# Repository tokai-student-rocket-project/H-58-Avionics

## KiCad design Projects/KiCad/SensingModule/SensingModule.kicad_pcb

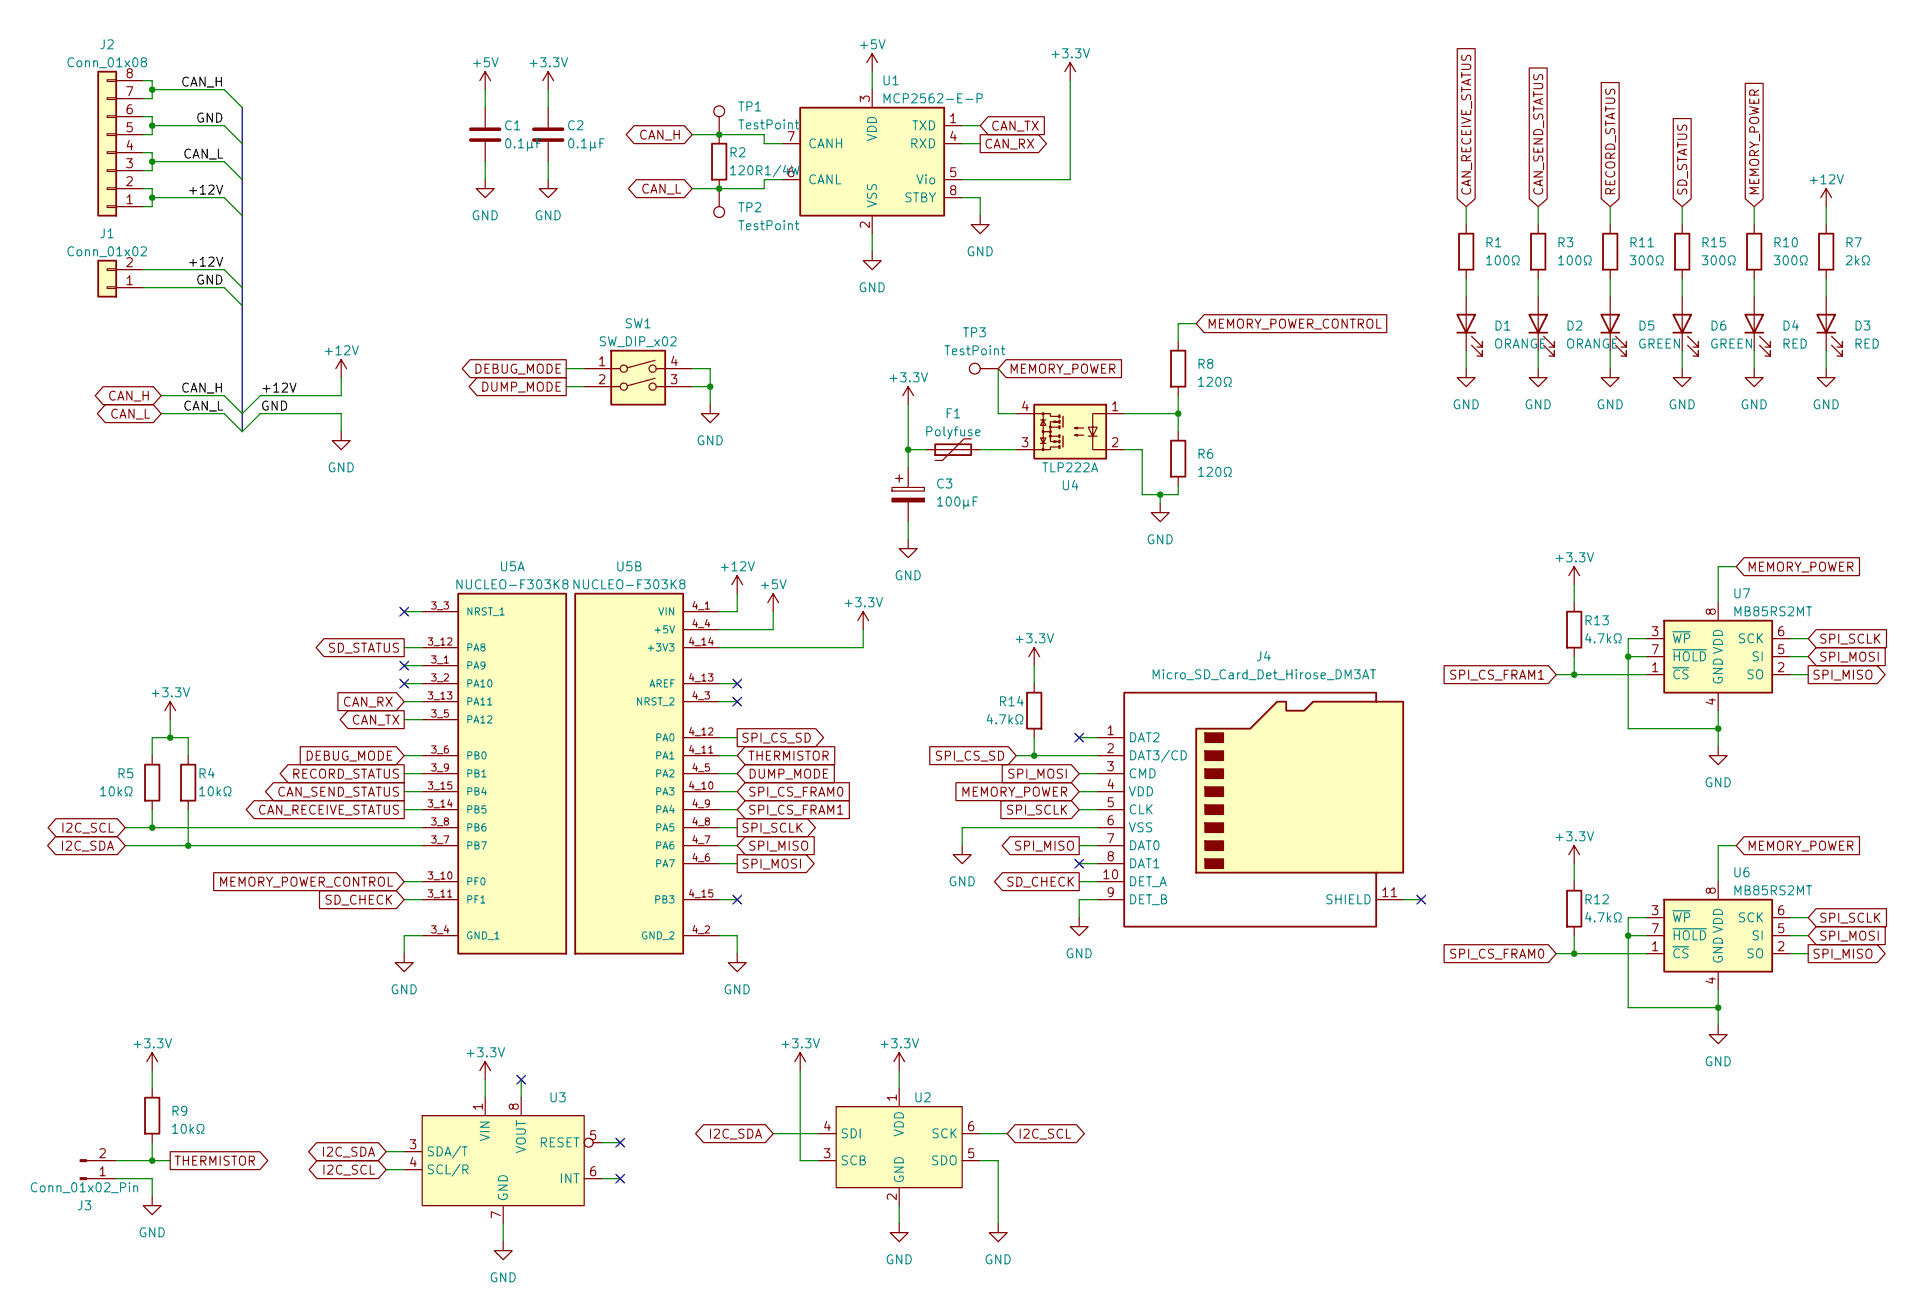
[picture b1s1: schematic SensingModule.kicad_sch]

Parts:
C1, C2: 0.1μF; C_0805_2012Metric_Pad1.18x1.45mm_HandSolder
C3: 100μF; CP_Elec_6.3x7.7
D1, D2: ORANGE; LED_0603_1608Metric_Pad1.05x0.95mm_HandSolder
D3, D4: RED; LED_0603_1608Metric_Pad1.05x0.95mm_HandSolder
D5, D6: GREEN; LED_0603_1608Metric_Pad1.05x0.95mm_HandSolder
F1: Polyfuse; Fuse_1206_3216Metric_Pad1.42x1.75mm_HandSolder
J1: Conn_01x02; Hirose_DF1B
J2: Conn_01x08; Hirose_DF11-8DP-2DSA_2x04_P2.00mm_Vertical
J3: Conn_01x02_Pin; Hirose_DF1B
J4: Micro_SD_Card_Det_Hirose_DM3AT; microSD_HC_Hirose_DM3AT-SF-PEJM5
R1, R3: 100Ω; R_0603_1608Metric_Pad0.98x0.95mm_HandSolder
R2: 120R1/4W; R_0603_1608Metric_Pad0.98x0.95mm_HandSolder
R4, R5, R9: 10kΩ; R_0603_1608Metric_Pad0.98x0.95mm_HandSolder
R6, R8: 120Ω; R_0603_1608Metric_Pad0.98x0.95mm_HandSolder
R7: 2kΩ; R_0603_1608Metric_Pad0.98x0.95mm_HandSolder
R10, R11, R15: 300Ω; R_0603_1608Metric_Pad0.98x0.95mm_HandSolder
R12, R13, R14: 4.7kΩ; R_0603_1608Metric_Pad0.98x0.95mm_HandSolder
SW1: SW_DIP_x02; SW_DIP_SPSTx02_Piano_10.8x6.64mm_W7.62mm_P2.54mm
TP1, TP2, TP3: TestPoint; Pin_D1.0mm_L10.0mm
U1: MCP2562-E-P; DIP-8_W7.62mm
U2: BME280
U3: BNO055
U4: TLP222A; DIP-4_W7.62mm
U5: NUCLEO-F303K8; MODULE_NUCLEO-F303K8; PARTREV 5
U6, U7: MB85RS2MT; DIP-8_W7.62mm

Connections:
+3.3V: C2.1, C3.1, F1.1, R4.1, R5.1, R9.1, R12.1, R13.1, R14.1, U1.5 (Vio), U2.1 (VDD), U2.3 (SCB), U3.1 (VIN), U5.4_14 (+3V3)
+5V: C1.1, U1.3 (VDD), U5.4_4 (+5V)
+12V: J1.2, J2.1, J2.2, R7.1, U5.4_1 (VIN)
CAN_H: J2.7, J2.8, R2.1, TP1.1, U1.7 (CANH)
CAN_L: J2.3, J2.4, R2.2, TP2.1, U1.6 (CANL)
CAN_RECEIVE_STATUS: R1.1, U5.3_14 (PB5)
CAN_RX: U1.4 (RXD), U5.3_13 (PA11)
CAN_SEND_STATUS: R3.1, U5.3_15 (PB4)
CAN_TX: U1.1 (TXD), U5.3_5 (PA12)
DEBUG_MODE: SW1.1, U5.3_6 (PB0)
DUMP_MODE: SW1.2, U5.4_5 (PA2)
GND: C1.2, C2.2, C3.2, D1.1 (K), D2.1 (K), D3.1 (K), D4.1 (K), D5.1 (K), D6.1 (K), J1.1, J2.5, J2.6, J3.1, J4.6 (VSS), J4.9 (DET_B), R6.2, SW1.3, SW1.4, U1.2 (VSS), U1.8 (STBY), U2.2 (GND), U2.5 (SDO), U3.7 (GND), U4.2, U5.3_4 (GND_1), U5.4_2 (GND_2), U6.3 (~WP), U6.4 (GND), U6.7 (~HOLD), U7.3 (~WP), U7.4 (GND), U7.7 (~HOLD)
I2C_SCL: R5.2, U2.6 (SCK), U3.4 (SCL/R), U5.3_8 (PB6)
I2C_SDA: R4.2, U2.4 (SDI), U3.3 (SDA/T), U5.3_7 (PB7)
MEMORY_POWER: J4.4 (VDD), R10.1, TP3.1, U4.4, U6.8 (VDD), U7.8 (VDD)
MEMORY_POWER_CONTROL: R8.1, U5.3_10 (PF0)
unnamed: D1.2 (A), R1.2
unnamed: D2.2 (A), R3.2
unnamed: D3.2 (A), R7.2
unnamed: D4.2 (A), R10.2
unnamed: D5.2 (A), R11.2
unnamed: D6.2 (A), R15.2
unnamed: F1.2, U4.3
unnamed: R6.1, R8.2, U4.1
RECORD_STATUS: R11.1, U5.3_9 (PB1)
SD_CHECK: J4.10 (DET_A), U5.3_11 (PF1)
SD_STATUS: R15.1, U5.3_12 (PA8)
SPI_CS_FRAM0: R12.2, U5.4_10 (PA3), U6.1 (~CS)
SPI_CS_FRAM1: R13.2, U5.4_9 (PA4), U7.1 (~CS)
SPI_CS_SD: J4.2 (DAT3/CD), R14.2, U5.4_12 (PA0)
SPI_MISO: J4.7 (DAT0), U5.4_7 (PA6), U6.2 (SO), U7.2 (SO)
SPI_MOSI: J4.3 (CMD), U5.4_6 (PA7), U6.5 (SI), U7.5 (SI)
SPI_SCLK: J4.5 (CLK), U5.4_8 (PA5), U6.6 (SCK), U7.6 (SCK)
THERMISTOR: J3.2, R9.2, U5.4_11 (PA1)

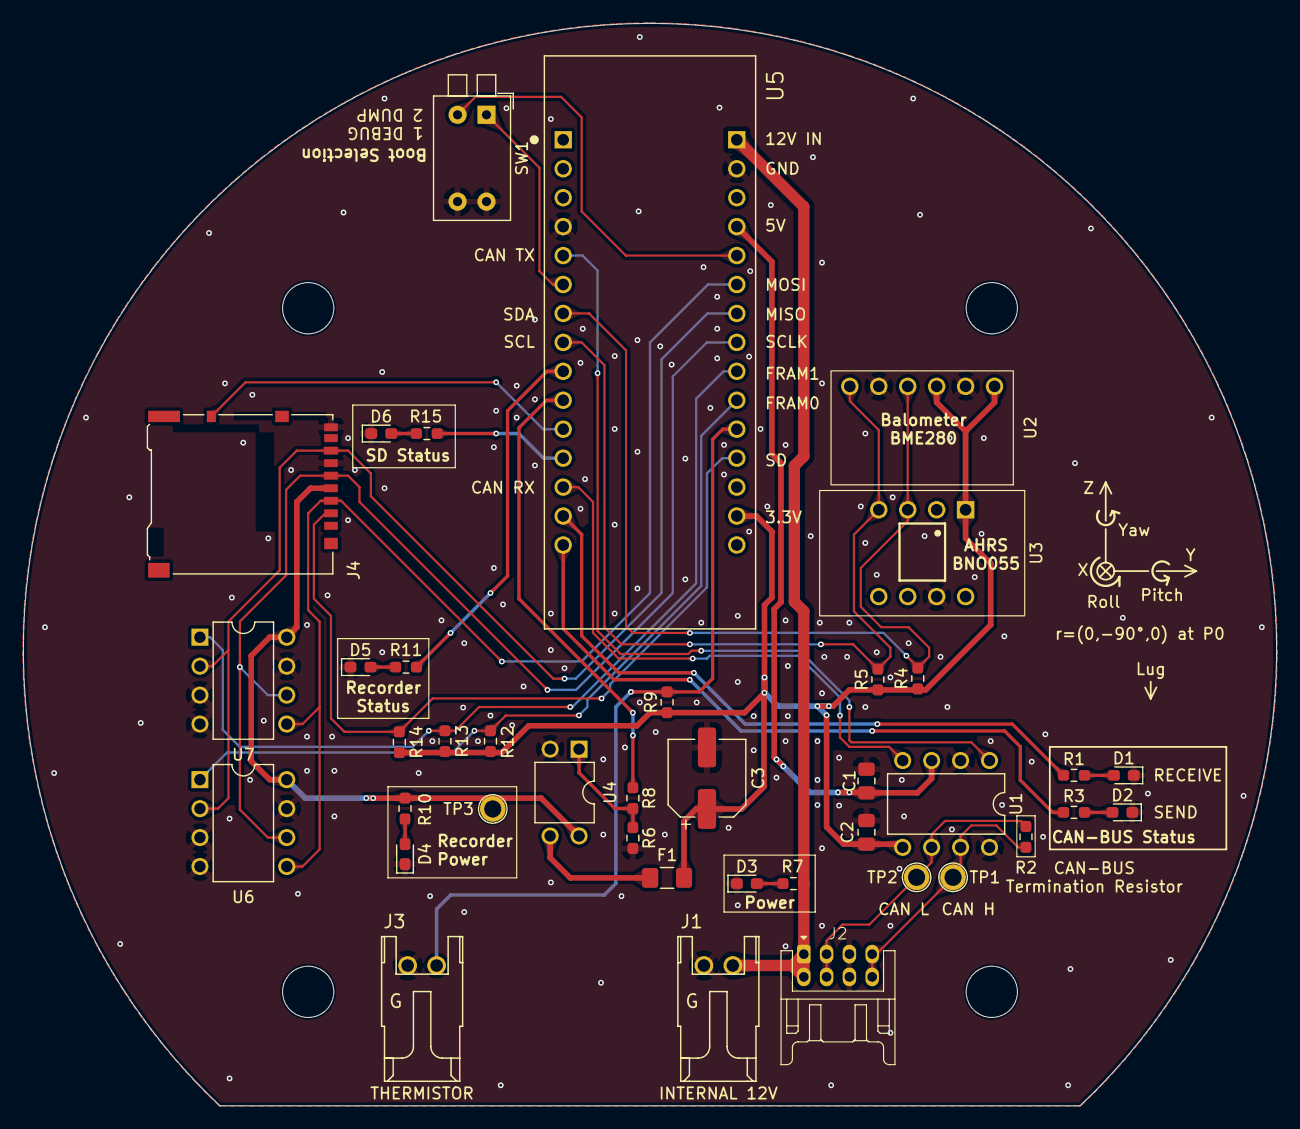
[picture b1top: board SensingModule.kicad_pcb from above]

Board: 2 copper layers, 110.0 x 95.0 mm, 40 parts (0 on the bottom side), 34 nets.

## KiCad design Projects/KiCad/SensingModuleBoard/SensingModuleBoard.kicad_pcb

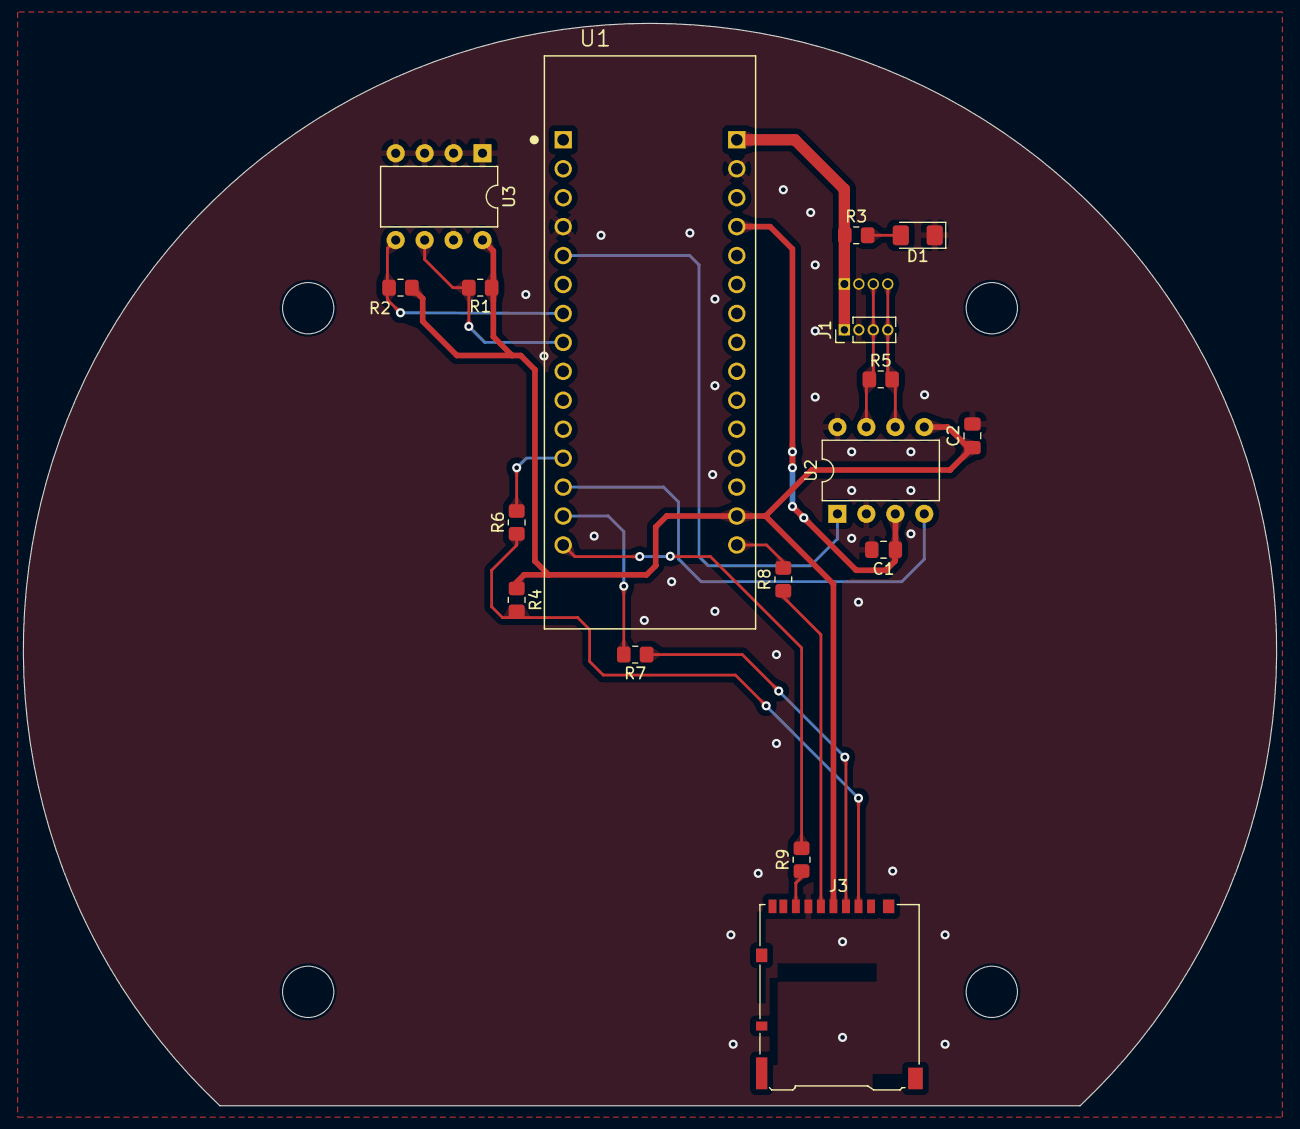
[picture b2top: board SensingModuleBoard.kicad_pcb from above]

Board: 2 copper layers, 110.0 x 95.0 mm, 18 parts (1 on the bottom side), 19 nets.

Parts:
C1, C2: 0.1μF; C_0805_2012Metric_Pad1.18x1.45mm_HandSolder
D1: LED; LED_1206_3216Metric_Pad1.42x1.75mm_HandSolder
J1: Conn_01x04_Pin; PinHeader_1x04_P1.27mm_Vertical
J2: Conn_01x04_Socket; PinSocket_1x04_P1.27mm_Vertical
J3: Micro_SD_Card_Det_Hirose_DM3AT; microSD_HC_Hirose_DM3AT-SF-PEJM5
R1, R2: 2.2kΩ; R_0805_2012Metric_Pad1.20x1.40mm_HandSolder
R3: 2kΩ; R_0805_2012Metric_Pad1.20x1.40mm_HandSolder
R4: 4.7kΩ; R_0805_2012Metric_Pad1.20x1.40mm_HandSolder
R5: 120R1/4W; R_0805_2012Metric_Pad1.20x1.40mm_HandSolder
R6, R7, R8, R9: 22Ω; R_0805_2012Metric_Pad1.20x1.40mm_HandSolder
U1: NUCLEO-F303K8; MODULE_NUCLEO-F303K8
U2: MCP2562-E-P; DIP-8_W7.62mm
U3: 24LC256; DIP-8_W7.62mm

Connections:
+3.3V: C2.1, J3.4 (VDD), R1.1, R2.1, R4.1, U1.4_14 (+3V3), U2.5 (Vio), U3.8 (VCC)
+5V: C1.1, U1.4_4 (+5V), U2.3 (VDD)
+12V: J1.1, J2.1, R3.1, U1.4_1 (VIN)
CAN_H: J1.3, J2.3, R5.1, U2.7 (CANH)
CAN_L: J1.4, J2.4, R5.2, U2.6 (CANL)
CAN_RX: U1.3_13 (PA11), U2.4 (RXD)
CAN_TX: U1.3_5 (PA12), U2.1 (TXD)
GND: C1.2, C2.2, D1.1 (K), J1.2, J2.2, J3.6 (VSS), U1.3_4 (GND_1), U1.4_2 (GND_2), U2.2 (VSS), U2.8 (STBY), U3.1 (A0), U3.2 (A1), U3.3 (A2), U3.4 (GND), U3.7 (WP)
I2C_SCL: R1.2, U1.3_8 (PB6), U3.6 (SCL)
I2C_SDA: R2.2, U1.3_7 (PB7), U3.5 (SDA)
unnamed: D1.2 (A), R3.2
unnamed: J3.7 (DAT0), R9.1
unnamed: R6.2, U1.3_12 (PA8)
unnamed: R7.2, U1.3_14 (PB5)
unnamed: R8.2, U1.4_15 (PB3)
SPI_CS_SD: J3.2 (DAT3/CD), R4.2, R6.1
SPI_MISO: R9.2, U1.3_15 (PB4)
SPI_MOSI: J3.3 (CMD), R7.1
SPI_SCLK: J3.5 (CLK), R8.1

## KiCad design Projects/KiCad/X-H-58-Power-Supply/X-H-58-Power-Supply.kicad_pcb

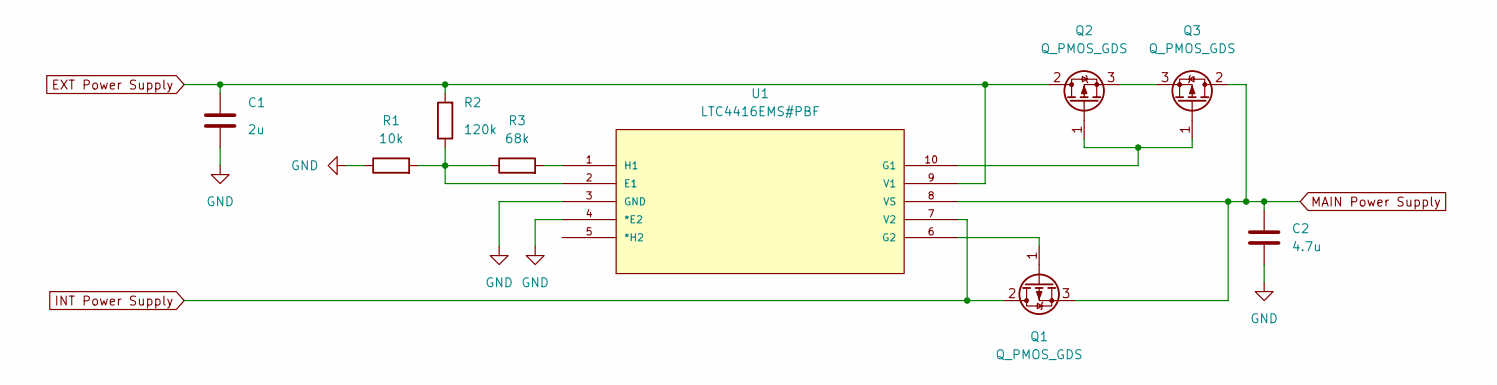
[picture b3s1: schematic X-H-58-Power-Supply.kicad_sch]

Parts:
C1: 2u; C_0603_1608Metric_Pad1.08x0.95mm_HandSolder
C2: 4.7u; C_0603_1608Metric_Pad1.08x0.95mm_HandSolder
Q1, Q2, Q3: Q_PMOS_GDS; TO-252-2
R1: 10k; R_0603_1608Metric_Pad0.98x0.95mm_HandSolder
R2: 120k; R_0603_1608Metric_Pad0.98x0.95mm_HandSolder
R3: 68k; R_0603_1608Metric_Pad0.98x0.95mm_HandSolder
U1: LTC4416EMS#PBF; MSOP-10-1EP_3x3mm_P0.5mm_EP1.68x1.88mm_ThermalVias; MANUFACTURER_PART_NUMBER ltc4416ims1

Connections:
EXT Power Supply: C1.1, Q2.2 (D), R2.2, U1.9 (V1)
GND: C1.2, C2.2, R1.1, U1.3 (GND), U1.4 (*E2)
INT Power Supply: Q1.2 (D), U1.7 (V2)
MAIN Power Supply: C2.1, Q1.3 (S), Q3.2 (D), U1.8 (VS)
unnamed: Q1.1 (G), U1.6 (G2)
unnamed: Q2.3 (S), Q3.3 (S)
unnamed: R1.2, R2.1, R3.1, U1.2 (E1)
unnamed: R3.2, U1.1 (H1)
unnamed: Q2.1 (G), Q3.1 (G), U1.10 (G1)

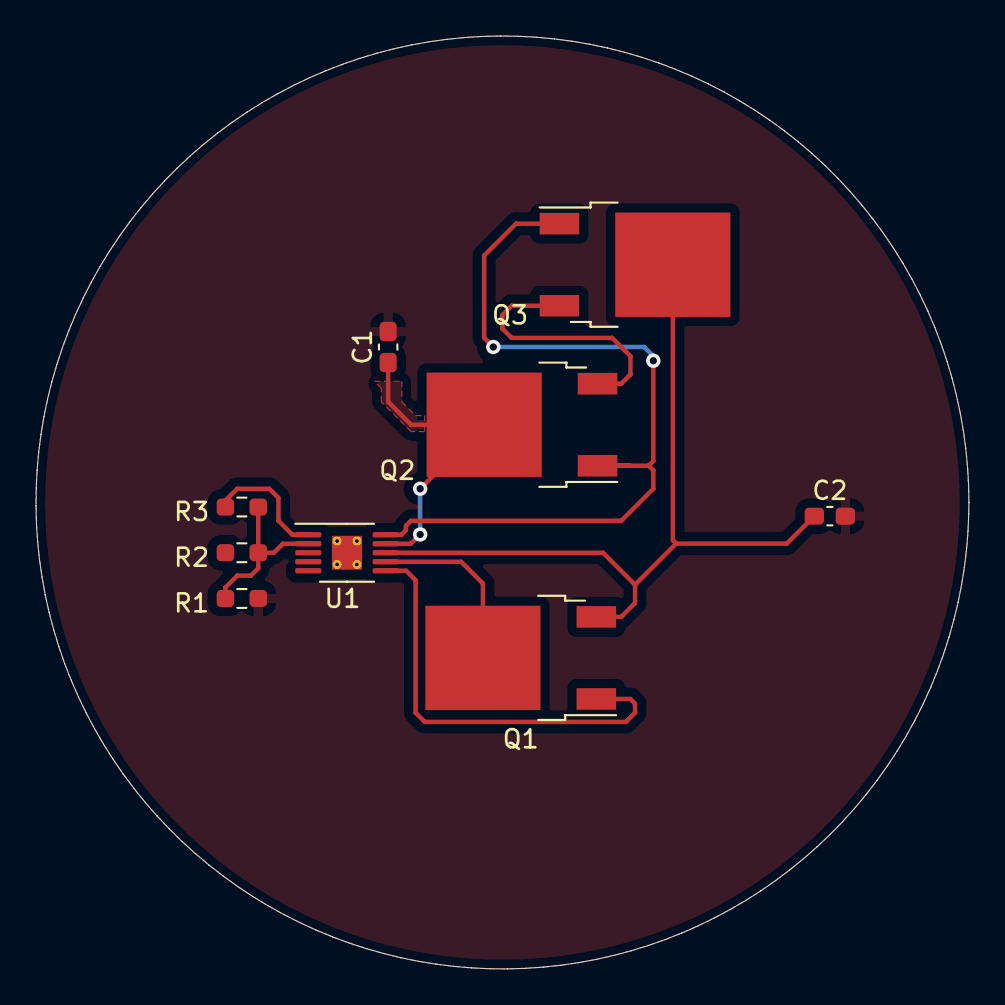
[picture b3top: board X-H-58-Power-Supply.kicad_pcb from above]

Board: 2 copper layers, 51.8 x 51.8 mm, 9 parts (0 on the bottom side), 9 nets.
